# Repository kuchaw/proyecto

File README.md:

Proyecto de la Escuela Secundaria de Educación Tecnica (ESETP) N°703 José Toschke de la ciudad de Puerto Madryn.
Este proyecto final es del area de electronica y el grupo a relizar el proyecto está conformado por Iñaki Lazcano, Juan Gonzalez y Camina Santiago.
El proyecto consta de un pequeño prototipo de satelite conocido como "CANSAT" diseñado para medir datos atmosfericos y participar en la competencia/muestra llevada a cabo por la UNSAM entre las fechas 24 y 27 de noviembre de 2026 en buenos aires.
El objetivo del cansat es la medicion de datos (humedad, temperatura, presión atmosferica, altitud, longitud, latitud) y el aterrizaje seguro del mismo luego de ser desplegado de un dron a aproximadamente 100 metros. El cansat debe ser capaz de operar en diferentes modos y enviar telemetría a una estacion terrena que debe ser capaz de analizar y almacenar los datos para un posteior analisis

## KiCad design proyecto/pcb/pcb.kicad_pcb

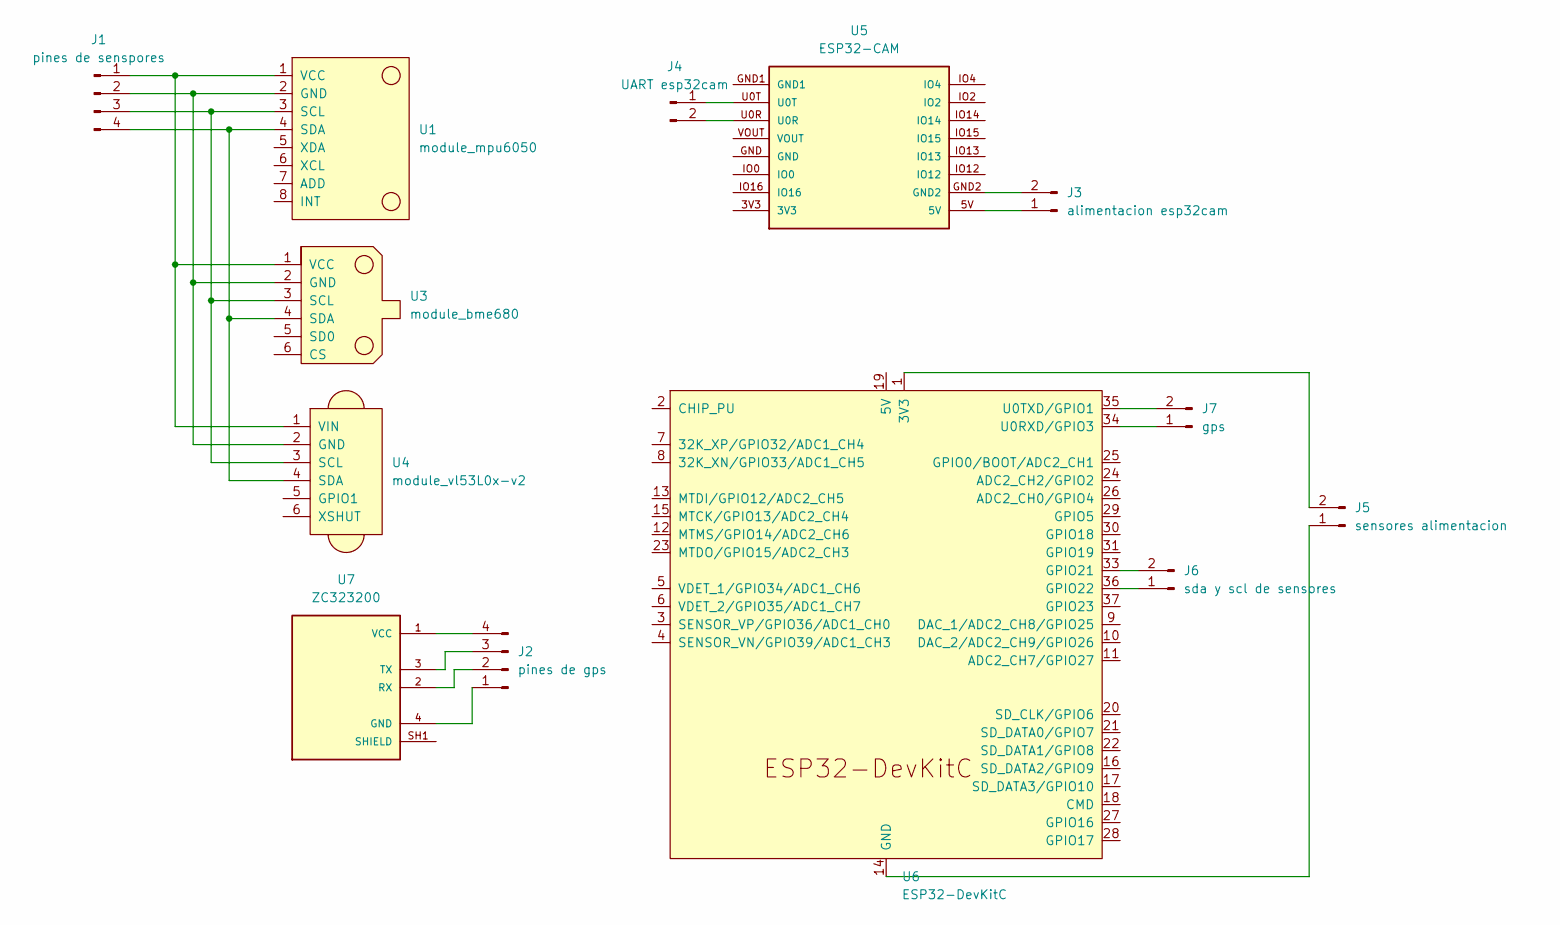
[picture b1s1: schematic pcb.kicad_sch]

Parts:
J1: pines de senspores; PinHeader_1x04_P1.00mm_Horizontal
J2: pines de gps; PinHeader_1x04_P1.00mm_Horizontal
J3: alimentacion esp32cam; PinHeader_1x02_P1.00mm_Horizontal
J4: UART esp32cam; PinHeader_1x02_P1.00mm_Horizontal
J5: sensores alimentacion; PinHeader_1x02_P1.00mm_Horizontal
J6: sda y scl de sensores; PinHeader_1x02_P1.00mm_Horizontal
J7: gps; PinHeader_1x02_P1.00mm_Horizontal
U1: module_mpu6050
U3: module_bme680
U4: module_vl53L0x-v2; module_vl53l0x
U5: ESP32-CAM
U6: ESP32-DevKitC
U7: ZC323200; XCVR_ZC323200; PARTREV N/A

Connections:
unnamed: J1.1, U1.1 (VCC), U3.1 (VCC), U4.1 (VIN)
unnamed: J1.2, U1.2 (GND), U3.2 (GND), U4.2 (GND)
unnamed: J1.3, U1.3 (SCL), U3.3 (SCL), U4.3 (SCL)
unnamed: J1.4, U1.4 (SDA), U3.4 (SDA), U4.4 (SDA)
unnamed: J2.1, U7.4 (GND)
unnamed: J2.2, U7.2 (RX)
unnamed: J2.3, U7.3 (TX)
unnamed: J2.4, U7.1 (VCC)
unnamed: J3.1, U5.5V
unnamed: J3.2, U5.GND2
unnamed: J4.1, U5.U0T
unnamed: J4.2, U5.U0R
unnamed: J5.1, U6.14 (GND), U6.32 (GND), U6.38 (GND)
unnamed: J5.2, U6.1 (3V3)
unnamed: J6.1, U6.36 (GPIO22)
unnamed: J6.2, U6.33 (GPIO21)
unnamed: J7.1, U6.34 (U0RXD/GPIO3)
unnamed: J7.2, U6.35 (U0TXD/GPIO1)
unnamed: U7.SH1 (SHIELD), U7.SH2 (SHIELD), U7.SH3 (SHIELD), U7.SH4 (SHIELD)

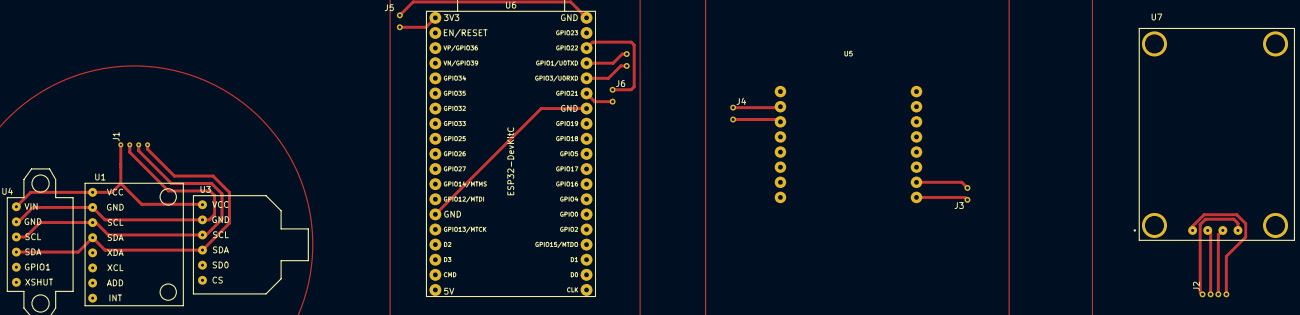
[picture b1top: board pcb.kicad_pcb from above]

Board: 2 copper layers, 13 parts (0 on the bottom side), 19 nets.

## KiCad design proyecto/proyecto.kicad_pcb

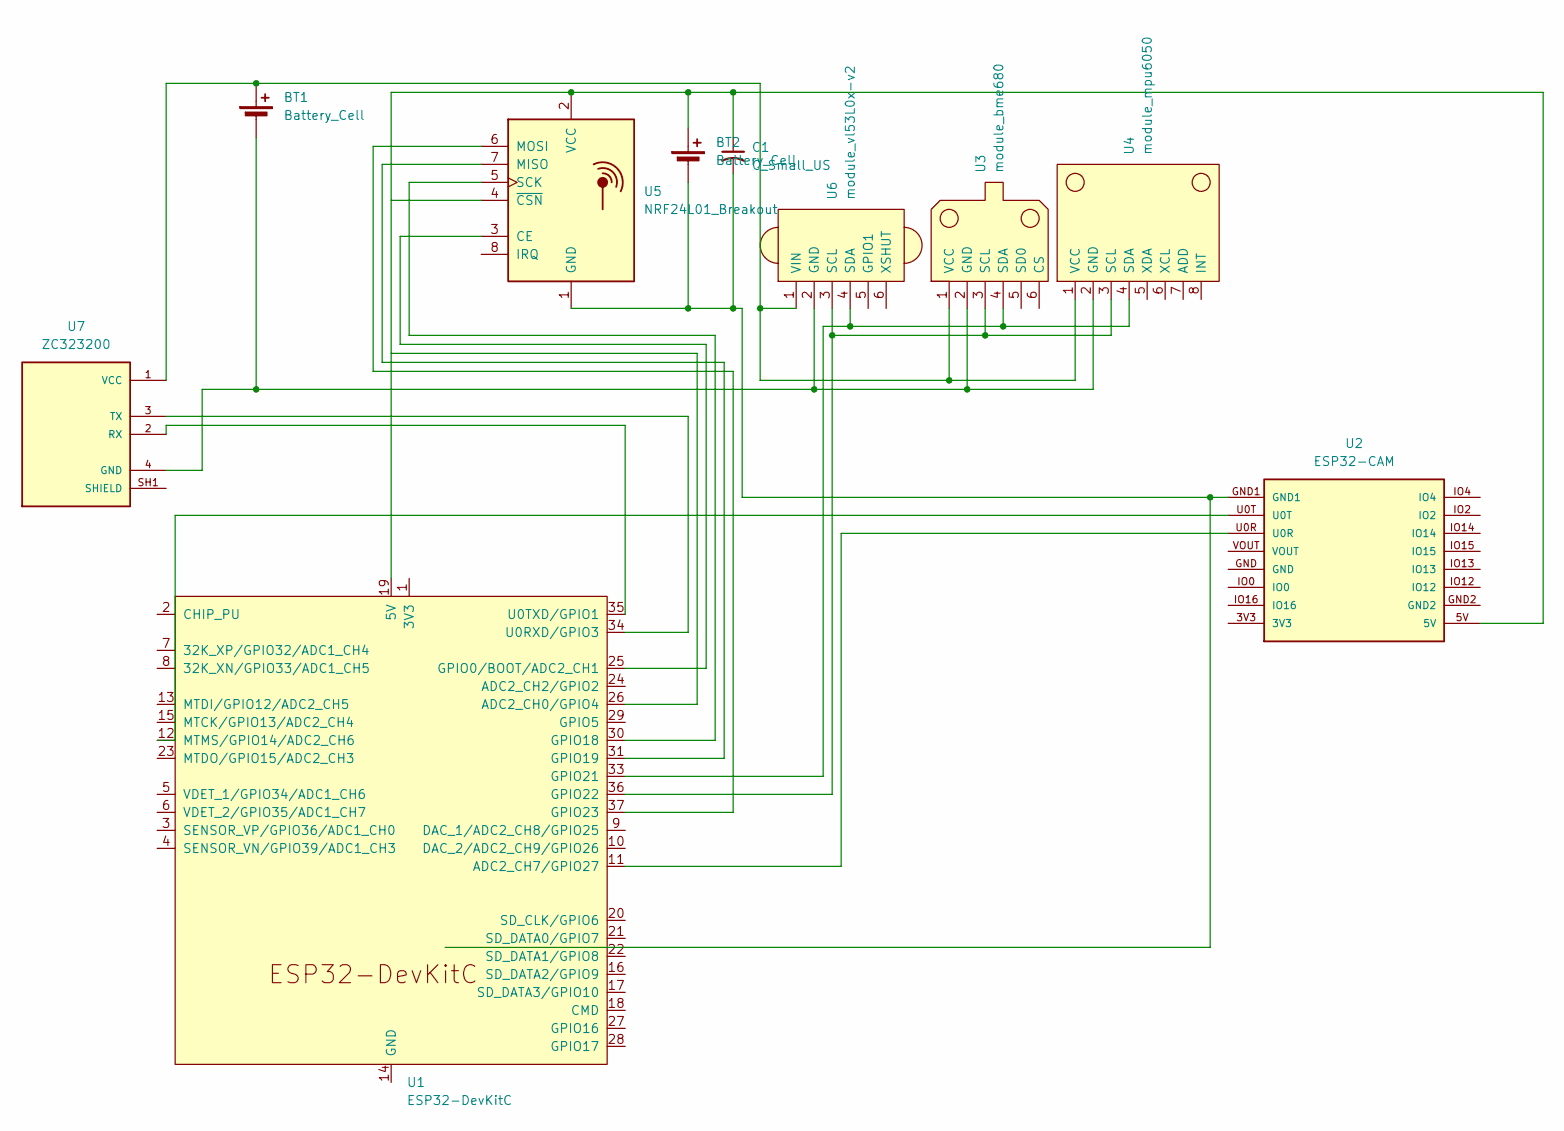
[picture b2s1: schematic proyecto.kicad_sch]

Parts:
BT1, BT2: Battery_Cell; PinHeader_1x02_P1.00mm_Horizontal
C1: C_Small_US; CP_Axial_L10.0mm_D4.5mm_P15.00mm_Horizontal
U1: ESP32-DevKitC
U2: ESP32-CAM
U3: module_bme680
U4: module_mpu6050
U5: NRF24L01_Breakout; nRF24L01_Breakout
U6: module_vl53L0x-v2; module_vl53l0x
U7: ZC323200; XCVR_ZC323200; PARTREV N/A

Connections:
unnamed: BT1.1 (+), U3.1 (VCC), U4.1 (VCC), U6.1 (VIN), U7.1 (VCC)
unnamed: BT1.2 (-), U3.2 (GND), U4.2 (GND), U6.2 (GND), U7.4 (GND)
unnamed: BT2.1 (+), C1.1, U1.19 (5V), U2.5V, U5.2 (VCC)
unnamed: BT2.2 (-), C1.2, U2.GND1, U5.1 (GND)
unnamed: U1.26 (ADC2_CH0/GPIO4), U5.4 (~CSN)
unnamed: U1.11 (ADC2_CH7/GPIO27), U2.U0R
unnamed: U1.14 (GND), U1.32 (GND), U1.38 (GND)
unnamed: U1.25 (GPIO0/BOOT/ADC2_CH1), U5.3 (CE)
unnamed: U1.30 (GPIO18), U5.5 (SCK)
unnamed: U1.31 (GPIO19), U5.7 (MISO)
unnamed: U1.33 (GPIO21), U3.4 (SDA), U4.4 (SDA), U6.4 (SDA)
unnamed: U1.36 (GPIO22), U3.3 (SCL), U4.3 (SCL), U6.3 (SCL)
unnamed: U1.37 (GPIO23), U5.6 (MOSI)
unnamed: U1.12 (MTMS/GPIO14/ADC2_CH6), U2.U0T
unnamed: U1.34 (U0RXD/GPIO3), U7.3 (TX)
unnamed: U1.35 (U0TXD/GPIO1), U7.2 (RX)
unnamed: U7.SH1 (SHIELD), U7.SH2 (SHIELD), U7.SH3 (SHIELD), U7.SH4 (SHIELD)

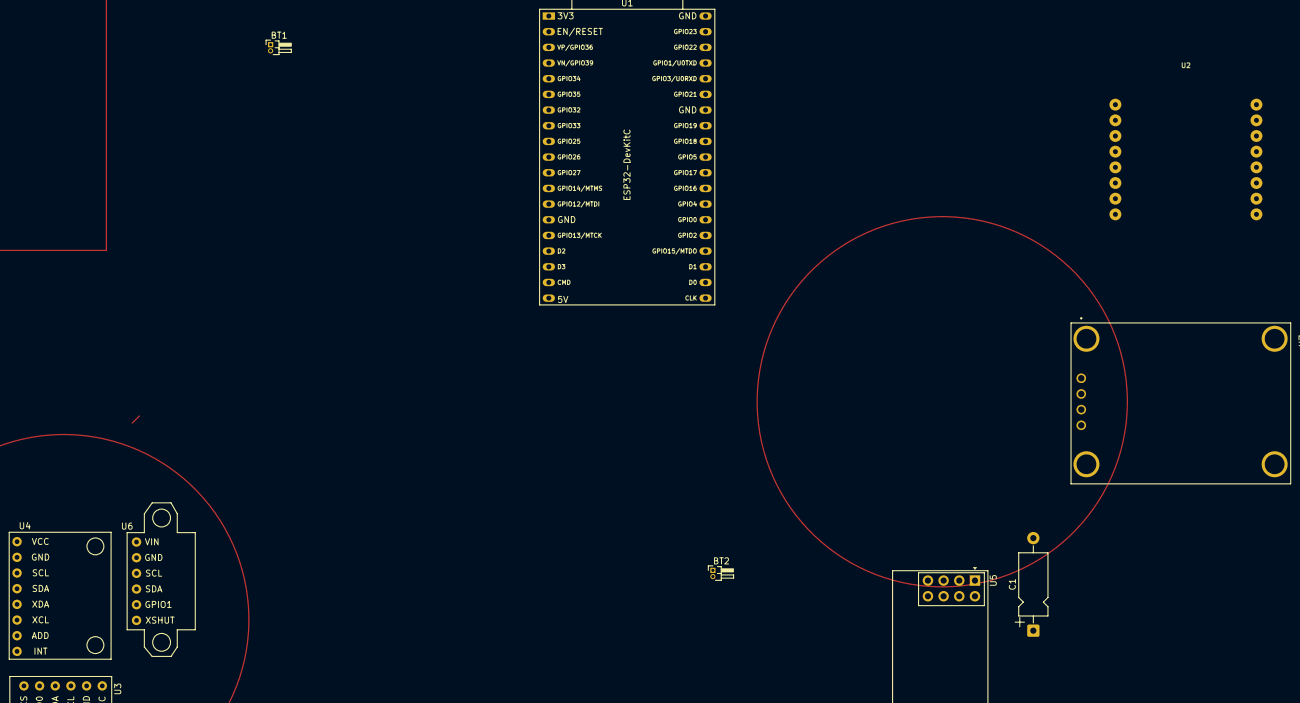
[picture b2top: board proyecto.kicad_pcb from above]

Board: 2 copper layers, 10 parts (0 on the bottom side), 17 nets.

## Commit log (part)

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2026-04-04 new file: mapa/mapa.html
2026-04-04 guardado de datos en archivo json y seguimiento de satelite mediante linea roja
2026-04-04 codigo labeed "gps" es el que se sube al esp32 de tierra!! puto el que lee
2026-04-04 controlador de memoria linea 25
2026-04-04 odificacin para hacer server publio
2026-04-04 debugging del web server en onrender
2026-04-04 still debugging for the onrender deployment
2026-04-05 README.md
2026-04-05 Revise project description in README.md
    Updated project description for clarity and detail.
2026-04-10 actualización de credenciales WiFi y endpoint del servidor en gps.ino; se agregó soporte para WiFiClientSecure, intento de mostrar rqtiquetas en el servidor web
2026-04-10 ehhhhh intento de que ande el html para que muestre etiquetas de temp, pres etc
2026-04-10 mejora en la visualización de telemetría: se agregaron nuevos datos (humedad, altitud, latitud, longitud, satélites, hora UTC) y se simplificó el formato de las tarjetas
2026-04-10 mejora en la estructura de visualización de telemetría: se organizaron las secciones de ambiente, GPS y hora con títulos descriptivos
2026-04-10 agregar cierre de div para la sección de hora en el HTML del mapa
2026-04-10 mejora en la estructura del HTML: se actualizaron los comentarios de las secciones de ambiente y hora a un formato más descriptivo
2026-04-10 los ultimos cuatro connits estoy intentado hacer que quede bien el formato de l apgina xd
2026-04-10 mas de lo mismo, debugging
2026-04-10 prueba de cartas de campos de mediicon cn valores dinamicos mediantes math.random.
2026-04-10 intento de que anden el menu de costado
2026-04-10 debugging
2026-04-10 +debugg.
2026-04-10 +debugg
2026-04-11 intento de tener todos los campos actualizados en las tarjetas de html con los sensores de verdad
2026-04-14 a traves del archivo: gps_sensores_httpost se ha logrado actualizar todos los datos del proyecto a tiempo real yse proyecta en el servidor web
2026-05-07 Codigos actualizados para el receptor en tierra y en el payload, modificacion del proyecto de un globo a un cansat
2026-05-07 eliminacion de los sensores ds y mpu puesto que no van a ser necesarios para el cansat
2026-05-07 Actualización del archivo readme
2026-05-07 Modificación del fronted para mostrar los datos correctos
2026-05-07 Modificación del html para que el frontend se vea bien
2026-05-11 debugging de pagina web para que muestre las cosas correctas en las etiquetas
2026-05-11 Corrección de la función de actualización de sensores ambientales y ajuste en la visualización de datos de temperatura en el mapa
2026-05-16 comienzo del desarrollo del modo pre_launch
